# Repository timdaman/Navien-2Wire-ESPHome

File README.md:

# navien-esphome

ESPHome replacement for the 2-wire wall remote of older **Navien NR-series** tankless water heaters (developed on an NR-210A).
It brings temperatures, burner and pump status, setpoint, power and **preheat (recirculation) control** into Home Assistant.

> ⚠️ Status: protocol decoded; the interface board is built, passes every bench test ([reference readings](hardware/bring-up.md#reference-readings-from-a-working-board)),
> and runs on a NR-210A (heater link, temperatures and burner status confirmed).
> The board only sends frames the original remote was seen sending.

## How it works

The board takes the place of the original 2Wire controls. It plugs into the same connector on the heater's control board (CN12, JST VH), so going back to stock controller is a matter of moving one plug.
See [docs/protocol.md](docs/protocol.md) for the bus details and [hardware/](hardware/) for the isolated interface board (schematics, parts, PCB).
For a part-by-part explanation of the board, see the [Detailed walkthrough of circuit operation](hardware/circuit-walkthrough.md). To test a built board, follow [hardware/bring-up.md](hardware/bring-up.md).
[Other ideas, untested](hardware/other-ideas.md) collects designs that were never built, such as a board that can listen alongside the original remote.

## ESPHome

The `navien_2wire` component should work on any board that ESPHome's `remote_receiver` / `remote_transmitter` support: Was tested with a ESP32 dev board. It needs two GPIOs, Ground, and 3.3 V.

Everything Navien-related is in one package file, [example/navien-package.yaml](example/navien-package.yaml).
Add it to any device's YAML and set the two pins:

```yaml
external_components:
  - source: github://<you>/navien-esphome
    components: [navien_2wire]

packages:
  navien: github://<you>/navien-esphome/example/navien-package.yaml   # or a local !include

substitutions:
  navien_rx_pin: GPIO4      # interface board RX (output of the H11L1)
  navien_tx_pin: GPIO5      # interface board TX (drives the PC817)
```

[example/navien-remote.yaml](example/navien-remote.yaml) is a complete dedicated-board config (shown for an ESP32-DevKitC).

### Pins

Use two of the chip's **internal** GPIOs. The receive pin needs edge interrupts (or RMT on ESP32).
**I2C/SPI port expanders (MCP23017, PCF8574, …) can't be used.** ESPHome rejects them for `remote_receiver`/`remote_transmitter`,
and the bus needs edge timing to about ±0.1 ms, which an I2C round trip can't deliver (see below).

* **ESP32 family:** RX and TX each use one RMT channel (shared with LED strips and IR). You can add `non_blocking: true` to the transmitter.
* **ESP8266 / RP2040:** the transmitter bit-bangs each 34 ms frame, briefly blocking the main loop about every 0.4 s. That's fine for a few other sensors, but on a very busy device prefer an ESP32.

### Why not a GPIO expander?

The bus sends a level change every 0.5 or 1 ms, and the receiver must time each edge to within about ±0.1 ms to tell them apart.
An expander only reports pin changes through an interrupt line followed by an I2C read: ≈0.1–0.3 ms at 400 kHz, plus however long the main loop takes to get around to it.
That's the same size as the margin, and transmitting would need a timed I2C write every 0.5 ms for 34 ms at a stretch.

The interface board's 3V3 pin can come from any 3.3 V supply on the device (it draws a few mA). The heater bus is fully **galvanically isolated**, there are no ground connections between the microcontroller and heater.

### Entities

Every entity is optional. The package enables all the useful ones:

| Platform | Keys |
|---|---|
| `sensor` | `outlet_temperature`, `inlet_temperature`, `status_raw`, `register_d3`, `frames_ok`, `frames_bad` |
| `binary_sensor` | `burner`, `pump`, `demand`, `heater_link` |
| `switch` | `power`, `preheat` |
| `number` | `setpoint` (`min_value` / `max_value`, default 98–140 °F; the steps aren't even, see [Setpoint steps](#setpoint-steps)) |

The board is the bus master: it starts polling the heater as soon as it boots, like the original remote. Setpoint, power and preheat are saved in flash
(defaults on first boot: 120 °F, power on, preheat off).
Heater does not transmit it's internal settings so set point, power and preheat status are managed blindly. Heater reports measured values; burner status, demand, and internal temperatures.

### Setpoint steps

The setpoint doesn't go up in even steps. Like the original remote, it moves **1 °F at a time up to 120 °F, then 5 °F at a time**:

| Range | Step | Values the heater can be sent |
|---|---|---|
| 98–120 °F | 1 °F | 98, 99, 100, … 119, 120 |
| 120–140 °F | 5 °F | 125, 130, 135, 140 |

Home Assistant's slider still moves 1 °F at a time across the whole range, because an ESPHome number can only have one step size.
When you pick a value between the 5 °F steps, the board rounds it to the nearest valid one, sends that, and the slider jumps to it:

| You set | Heater gets |
|---|---|
| 121 or 122 | 120 |
| 123 to 127 | 125 |
| 128 to 132 | 130 |
| 133 to 137 | 135 |
| 138 to 140 | 140 |

An automation that sets, say, 124 °F will see the setpoint read back as 125 °F. Use one of the values in the first table to avoid that.

Two more limits:

* **DIP switches 7/8 on the heater board cap the maximum** at 110, 120, 130 or 140 °F. The heater doesn't report this cap over the bus,
  so if you set a setpoint above it, HA shows your value but the heater quietly uses its cap. Check the switches (power off first)
  and set `max_value` to match, so HA only offers what the heater will actually do.
* **Water above 125 °F can scald.** Set `max_value` lower if that's a concern.

### Fail-safes and operating mode (optional)

[example/navien-failsafe.yaml](example/navien-failsafe.yaml) adds a **Navien operating mode** select (saved in flash) and keeps the heater
working sensibly when Home Assistant is down. Add it after the main package:

```yaml
packages:
  navien: !include navien-package.yaml
  navien_failsafe: !include navien-failsafe.yaml
```

| Mode | When chosen | 2 min after boot, or HA gone for 5 min |
|---|---|---|
| Off | power off, preheat off | nothing |
| On | power on, preheat off | power on, preheat off |
| On + preheat | power on, preheat on | power on, preheat on |
| Auto | power on; HA controls preheat | power on, preheat on |

ESPHome counts any API client as "connected", including the dashboard's log viewer, so the 5-minute timer doesn't run while you watch the logs.
In Auto mode, have your HA automation also trigger when `switch.navien_preheat` becomes available, so it re-applies preheat after an outage.

## Repository

```
components/          ESPHome external components: navien_2wire (use this), navien_2wire_b (untested, see hardware/other-ideas.md)
example/             example device config
hardware/            schematics, parts, wiring lists, PCB, and a circuit walkthrough
docs/protocol.md     bus protocol
tests/               codec test (real bus frames, including late-edge ones, + 40k jittered round trips)
tools/               Rigol SCPI capture / Manchester decode scripts used for the reverse engineering
```

Disclaimer: This is a personal project. The views, code, and opinions expressed here are my own and do not represent those of my current or past employers.

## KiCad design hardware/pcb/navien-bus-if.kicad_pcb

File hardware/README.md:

# Hardware

The board **replaces the wall remote**. The remote's cable plugs into connector **CN12** on the heater's control board.
The ESP board has a premade VH pigtail soldered on, so swapping between the remote and the board means moving one plug.

## Connecting to the heater

| | |
|---|---|
| Heater connector | **CN12**, silk-screened `Remote_Controller`, on the main control board (NR-210A) |
| Type | **JST VH**, 2-pin, 3.96 mm pitch. Mating plug: **VHR-2N**. Easiest: a premade VH 2-pin female pigtail ("VH3.96 2P with wires"), soldered to the board |
| Pin A (+) | **right-hand pin** when looking at the connector with its latch side down |
| Pin B (−) | left-hand pin |
| Protection on the heater side | FRM1 / FRM2: fusible resistors in series with both lines |

The remote's cable with its VH plug, and plugged into CN12:

**Reversed wiring is safe.** If A and B are swapped, the board's 15 V zener (D2) conducts forward and holds the line near 0.8 V.
The heater limits the current to ~12.5 mA and nothing sees more than ~0.8 V in reverse. It just won't communicate: the *Heater link* sensor stays off.
Flip the wires and it works. To check with a meter: with the original remote connected, A is the wire that reads **+6.5 to 8 V** relative to B.

**Power:** CN12 can't power the ESP board (the line delivers ~85 mW), so the ESP board needs its own supply, usually USB. The interface board takes its 3.3 V from the ESP board.

The interface board uses two optocouplers, one transistor and a handful of passives (about 14 parts).
It is **isolated**: the ESP board never shares ground with the heater, so any USB supply, a laptop, or a device shared with other sensors is fine.

How the bus works (details in [../docs/protocol.md](../docs/protocol.md)): the heater feeds the line with a ~12.5 mA current source (≈20 V open circuit).
The remote **clamps** it to ≈6.5 V. To send a '1', the heater raises its current to ≈24 mA (the clamp rises to ≈8 V), and the remote **releases** its clamp (the line rises to ≈15 V).
The board copies the original remote's clamp: ≈4.7 V zener + ≈130 Ω.

---

## Interface board

> New to electronics? The **[Detailed walkthrough of circuit operation](circuit-walkthrough.md)** explains what every part on this board does, with the numbers.

### Bus side (isolated from the ESP)

### ESP side

* **Idle:** R3 biases Q1 on from the bus itself, so the clamp D1 + R1 + R2 holds ≈6.5 V. This is also what the heater sees if the ESP crashes or loses power: a quiet remote.
* **Receive:** the clamp current flows through R2 (82 Ω, the sense resistor). At idle (13 mA) R2 drops 1.1 V, too little to light the H11L1's LED through R4. When the heater sends (24 mA), R2 drops 2.0 V, the LED gets ≈2.5 mA, and the H11L1 (with its Schmitt-trigger output) pulls the RX pin low.
* **Transmit:** the TX pin HIGH lights the PC817, which pulls Q1's base low and opens the clamp. The heater's current then flows into D2 and the line rises to ≈15 V, a '1' to the heater. The PC817 switches in microseconds, comfortably fast for the 500 µs half-bit.

<details>
<summary><b>Why two different optocouplers?</b> (Can't both be the same part?)</summary>

<br>

They do different jobs, and neither part does the other's job well.

**Receive needs a threshold (H11L1).** The heater's signal is only a 0.9 V swing across R2 (1.1 V idle → 2.0 V sending). The H11L1 switches at a fixed LED current (≤ 1.6 mA) with hysteresis and a clean logic edge, the same on every part.
A PC817 here would act as an analog part. Its output follows its LED current, and its CTR spreads from 50 % to 600 % between parts, so the switching point would differ from board to board.
At idle its LED would already be partly on, so the RX pin would see slow, half-on edges with no hysteresis. Manchester decoding relies on edge timing, so that eats into the margin.

**Transmit is just a switch (PC817).** About 9 mA into the LED drives the output far harder than Q1's base needs (~0.6 mA through R3), even with a low-CTR part, and microsecond switching is plenty at 1 kbit/s.
An H11L1 here would need its own supply on the *bus* side, where its output is, and there isn't one. Feeding it from the bus would put it near its 16 V limit while transmitting.
It would also take a few mA from the heater's 12.5 mA current source, which shifts the receive thresholds.

**Using two PC817s** is possible only with a Schmitt buffer (e.g. 74HC14) added before the RX pin, which adds a part instead of removing one. PC817s cost cents and are sold singly or in small packs, so keeping both parts is the simpler option.

</details>

| Ref | Qty | Part | Notes |
|---|---|---|---|
| U1 | 1 | **H11L1** (DIP-6) | optocoupler with Schmitt-trigger output. 1 = LED anode, 2 = LED cathode, 4 = OUT, 5 = GND, 6 = VCC |
| U2 | 1 | **PC817** (DIP-4) | 1 = anode, 2 = cathode, 3 = emitter, 4 = collector |
| Q1 | 1 | 2N3904 | |
| D1 | 1 | 1N4732A | 4.7 V 1 W zener, band toward the bus + |
| D2 | 1 | 1N4744A | 15 V 1 W zener, band toward the bus + |
| D3 | 1 | P6KE24CA (through-hole) or SMBJ24A | 24 V bidirectional TVS (the PCB uses the P6KE24CA) |
| F1 | 1 | PTC fuse, 50 mA hold | e.g. Bel Fuse 0ZRE0005FF (the PCB footprint) |
| R1 | 1 | 47 Ω | trims the idle voltage, 39–56 Ω |
| R2 | 1 | 82 Ω 1 % | sense resistor (can be made from prallel 100 Ω + 470 Ω) |
| R3 | 1 | 10 kΩ | |
| R4 | 1 | 330 Ω | H11L1 LED |
| R5 | 1 | 4.7 kΩ | pull-up to 3.3 V |
| R6 | 1 | 220 Ω | PC817 LED (~9 mA from 3.3 V) |
| C1 | 1 | 100 nF | H11L1 VCC decoupling |
| J1 | 1 | Premade JST VH 2-pin female pigtail | soldered to the board; its plug goes onto CN12. A = wire on CN12's right pin (latch down) |
| — | 1 | ESPHome board: ESP32 (any model), ESP8266 or RP2040 | dedicated, or an existing device with two free GPIOs |
| — | 1 | 5 V USB supply, ≥ 1 A | |

**Wiring list, bus side** (each row is one node, and none of these touch ESP GND):

| Node | Joins |
|---|---|
| BUS_A | J1-1 via F1 · D1 cathode · D2 cathode · D3 · R3 |
| CLAMP_1 | D1 anode · R1 |
| SENSE_TOP | R1 · R2 · R4 |
| H11L1_A | R4 other end · U1 pin 1 |
| SENSE_BOT | R2 other end · Q1 collector · U1 pin 2 |
| Q1_BASE | R3 other end · Q1 base · U2 pin 4 |
| BUS_GND | J1-2 · Q1 emitter · D2 anode · D3 other end · U2 pin 3 |

**Wiring list, ESP side:**

| Node | Joins |
|---|---|
| 3V3 | ESP 3V3 · U1 pin 6 · R5 · C1 |
| RX | ESP RX pin · U1 pin 4 · R5 other end |
| TX_LED | ESP TX pin via R6 · U2 pin 1 |
| GND | ESP GND · U1 pin 5 · U2 pin 2 · C1 other end |

Keep a few millimetres between the bus-side and ESP-side copper (the PCB below keeps ≥ 4.7 mm).

### Ready-made PCB

A 67 × 46 mm two-layer, all-through-hole board in [pcb/](pcb/):

| File | Use |
|---|---|
| [`pcb/fab/navien-bus-if-gerbers.zip`](pcb/fab/navien-bus-if-gerbers.zip) | **Upload this to the PCB maker** (JLCPCB, PCBWay, OSH Park, …). Gerbers + Excellon drill files |
| [`pcb/fab/BOM.csv`](pcb/fab/BOM.csv) | parts to buy, by reference |
| [`pcb/navien-bus-if.kicad_pcb`](pcb/navien-bus-if.kicad_pcb) | KiCad 10 board, to view or edit |
| [`pcb/make_pcb.py`](pcb/make_pcb.py) | regenerates the board (placement, routing, pours) from the circuit |
| [`pcb/check_pcb.py`](pcb/check_pcb.py) | re-checks netlist vs. circuit, connectivity and isolation distance |

Order settings: 2 layers, 1.6 mm FR-4, 1 oz copper, any colour/finish. Default rules are fine: 0.4 mm tracks, 0.3 mm clearance, 0.4 mm smallest drill.
The board passes KiCad's DRC with no warnings, and its netlist was checked against the wiring list above.

Assembly notes:
* Zener bands (cathode) go toward the **K** marks. D3 (TVS) is bidirectional.
* U1's pin 1 is top-left. U2 is rotated: its pin 1 is bottom-right, on the ESP side.
* **No connector on the board.** Buy a premade **JST VH 2-pin female pigtail** (20–22 AWG leads). Its plug goes onto CN12, and its two wires are soldered to J1: feed each wire up through the big strain-relief hole at the board edge, then down into its pad. The wire on CN12's **right-hand pin (latch down) goes to A+**. Swapped wires do no harm, it just won't talk.
* J2 goes to the ESP board with jumper wires: 3V3 → 3.3 V, GND → GND, RX → the pin set as `navien_rx_pin`, TX → `navien_tx_pin`. Any of the chip's own GPIOs works (see the main README's Pins section); an I2C port expander does not.

---

## Bring-up

Test the board on the bench before connecting it to the heater. **Step-by-step instructions, with expected readings and troubleshooting, are in [bring-up.md](bring-up.md).**
In short, using a 20 V supply and a 1.1 kΩ resistor (or the supply's current limit, or an LM317L) as a fake heater:

1. **Idle:** A+ to B− reads **≈ 6.5 V** (trim R1 if needed).
2. **Receive:** adding ≈ 12 mA (1 kΩ from 20 V to A+) lifts the line to **≈ 8 V** and pulls **RX low**.
3. **Transmit:** TX high lifts the line to **≈ 15 V**.
4. **Fail-safe:** with the ESP side unpowered, the line still idles at ≈ 6.5 V.
5. **On the heater:** move the CN12 plug to the board and check *Heater link*, the temperatures, burner and pump. Anything odd? Move the plug back to the remote.

---

## Other ideas

[Other ideas, untested](other-ideas.md) has a comparator design with a listen-only mode, for sniffing the bus alongside the original remote, and the `navien_2wire_b` component that goes with it.
Neither has been built or tested.

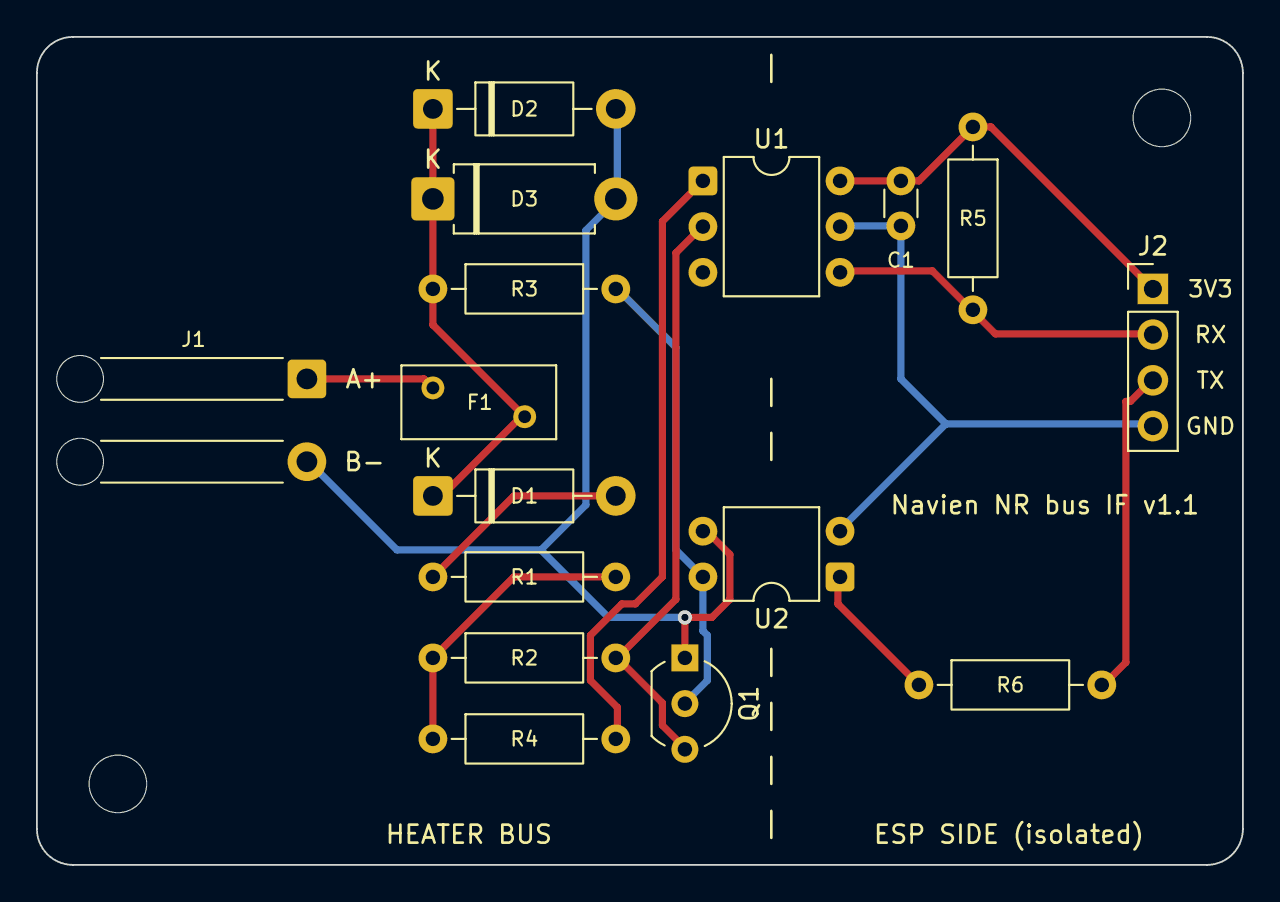
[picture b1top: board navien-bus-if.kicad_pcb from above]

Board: 2 copper layers, 67.0 x 46.0 mm, 18 parts (0 on the bottom side), 13 nets.

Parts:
C1: 100n; C_Disc_D3.0mm_W1.6mm_P2.50mm
D1: 1N4732A 4.7V; D_DO-41_SOD81_P10.16mm_Horizontal
D2: 1N4744A 15V; D_DO-41_SOD81_P10.16mm_Horizontal
D3: P6KE24CA; D_DO-15_P10.16mm_Horizontal
F1: 0ZRE0005FF 50mA PTC; Fuse_BelFuse_0ZRE0005FF_L8.3mm_W3.8mm
H1, H2: M3; MountingHole_3.2mm_M3
J1: VH pigtail to CN12; SolderWire-0.5sqmm_1x02_P4.6mm_D0.9mm_OD2.1mm_Relief
J2: to ESP board; PinHeader_1x04_P2.54mm_Vertical
Q1: 2N3904; TO-92_Inline_Wide
R1: 47; R_Axial_DIN0207_L6.3mm_D2.5mm_P10.16mm_Horizontal
R2: 82 1%; R_Axial_DIN0207_L6.3mm_D2.5mm_P10.16mm_Horizontal
R3: 10k; R_Axial_DIN0207_L6.3mm_D2.5mm_P10.16mm_Horizontal
R4: 330; R_Axial_DIN0207_L6.3mm_D2.5mm_P10.16mm_Horizontal
R5: 4.7k; R_Axial_DIN0207_L6.3mm_D2.5mm_P10.16mm_Horizontal
R6: 220; R_Axial_DIN0207_L6.3mm_D2.5mm_P10.16mm_Horizontal
U1: H11L1; DIP-6_W7.62mm
U2: PC817; DIP-4_W7.62mm

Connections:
+3V3: C1.1, J2.1, R5.1, U1.6
BUS_A: D1.1, D2.1, D3.1, F1.2, R3.1
BUS_A_IN: F1.1, J1.1
BUS_GND: D2.2, D3.2, J1.2, Q1.1, U2.3
CLAMP: D1.2, R1.1
GND: C1.2, J2.4, U1.5, U2.2
LED_A: R4.2, U1.1
Q1_BASE: Q1.2, R3.2, U2.4
RX: J2.2, R5.2, U1.4
SENSE_BOT: Q1.3, R2.2, U1.2
SENSE_TOP: R1.2, R2.1, R4.1
TX: J2.3, R6.2
TX_LED: R6.1, U2.1

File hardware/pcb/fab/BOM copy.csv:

Reference,Qty,Value,Part,Footprint,Notes
U1,1,H11L1,H11L1M (onsemi) or equivalent,DIP-6 7.62 mm,Schmitt-trigger optocoupler. Pin 1 dot toward J1 side top
U2,1,PC817,Sharp/Everlight PC817 or equivalent,DIP-4 7.62 mm,Pin 1 at bottom-right (ESP side)
Q1,1,2N3904,2N3904 TO-92,TO-92 inline wide (2.54 mm),Flat face per silkscreen
D1,1,1N4732A,4.7 V 1 W zener,DO-41,Band = K toward the K mark
D2,1,1N4744A,15 V 1 W zener,DO-41,Band = K toward the K mark
D3,1,P6KE24CA,24 V bidirectional TVS,DO-15,Either orientation
F1,1,0ZRE0005FF,Bel Fuse 0ZRE0005FF PTC 50 mA hold,Radial 5.1 mm,
R1,1,47,47 ohm 1/4 W,Axial 10.16 mm,
R2,1,82 1%,82 ohm 1% 1/4 W,Axial 10.16 mm,Sense resistor
R3,1,10k,10 kohm 1/4 W,Axial 10.16 mm,
R4,1,330,330 ohm 1/4 W,Axial 10.16 mm,
R5,1,4.7k,4.7 kohm 1/4 W,Axial 10.16 mm,
R6,1,220,220 ohm 1/4 W,Axial 10.16 mm,
C1,1,100n,100 nF ceramic,Disc 2.5 mm,
J1,1,VH pigtail,Premade JST VH 3.96 mm 2-pin FEMALE pigtail (VHR-2N housing with leads),Solder pads + strain relief,20-22 AWG leads. Feed each lead up through the large relief hole then solder into its pad. A+ to the wire on CN12's right pin (latch down)
J2,1,1x04 header,2.54 mm pin header 1x4,2.54 mm,Or solder wires
—,1,ESPHome board,ESP32 (any variant) / ESP8266 / RP2040 dev board,—,Wire 3V3/RX/TX/GND to J2 with jumper wires; can be an existing device
